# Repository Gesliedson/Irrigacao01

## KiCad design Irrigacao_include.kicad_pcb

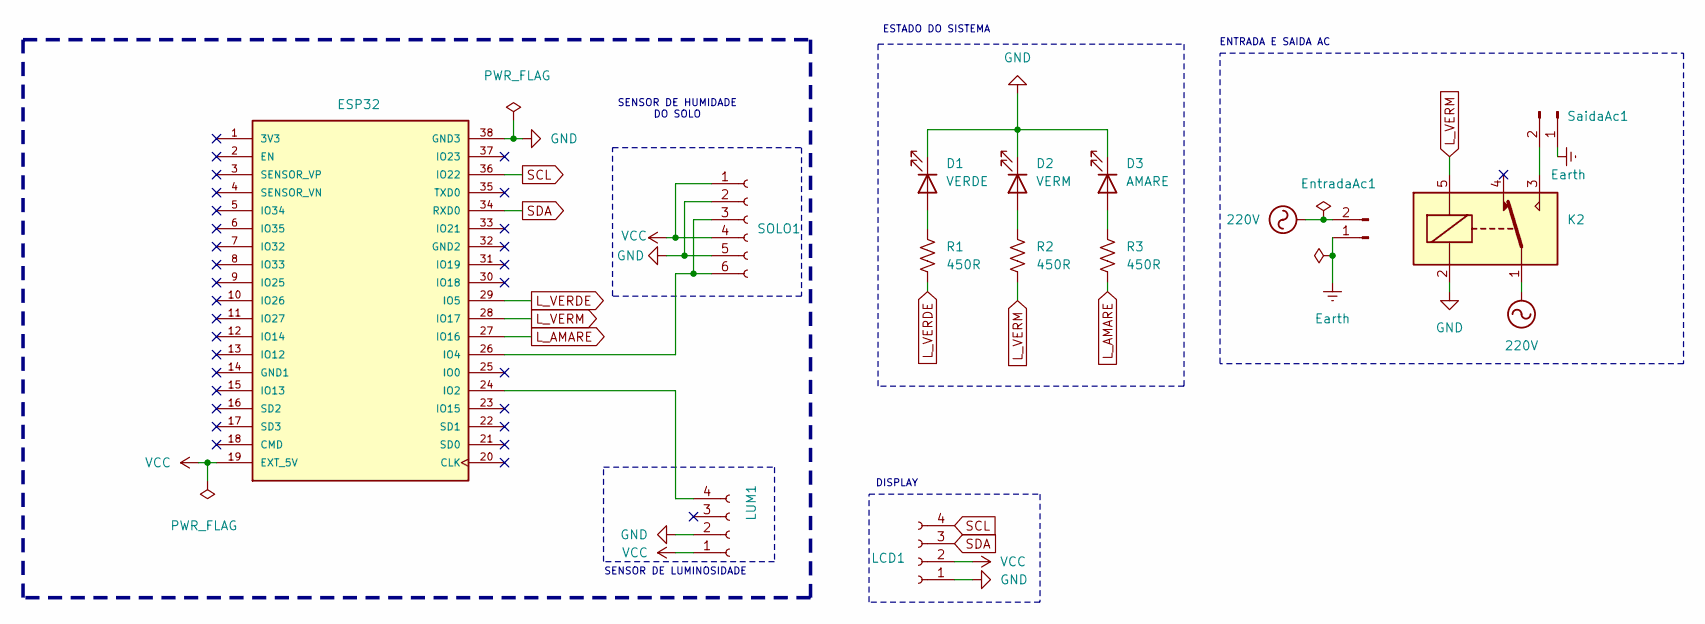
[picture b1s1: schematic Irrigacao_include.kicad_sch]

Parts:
D1: VERDE; LED_D3.0mm
D2: VERM; LED_D3.0mm
D3: AMARE; LED_D3.0mm
ESP32: DEVKIT_V1_ESP32-WROOM-32; MODULE_DEVKIT_V1_ESP32-WROOM-32; PARTREV N/A
EntradaAc1: Conn_01x02_Pin; PhoenixContact_GMSTBA_2,5_2-G_1x02_P7.50mm_Horizontal
K2: SANYOU_SRD_Form_C; Relay_SPDT_SANYOU_SRD_Series_Form_C
LCD1: Conn_01x04_Socket; PinSocket_1x04_P2.54mm_Horizontal
LUM1: Conn_01x04_Socket; PinSocket_1x04_P2.54mm_Horizontal
R1, R2, R3: 450R; R_Axial_DIN0207_L6.3mm_D2.5mm_P10.16mm_Horizontal
SOLO1: Conn_01x06_Socket; PinSocket_1x06_P2.54mm_Vertical
SaidaAc1: Conn_01x02_Pin; PhoenixContact_GMSTBA_2,5_2-G_1x02_P7.50mm_Horizontal

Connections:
220V: EntradaAc1.2, K2.1
Earth: EntradaAc1.1, SaidaAc1.1
GND: D1.1 (K), D2.1 (K), D3.1 (K), ESP32.38 (GND3), K2.2, LCD1.1, LUM1.2, SOLO1.2, SOLO1.5
L_AMARE: ESP32.27 (IO16), R3.2
L_VERDE: ESP32.29 (IO5), R1.2
L_VERM: ESP32.28 (IO17), K2.5, R2.2
unnamed: D1.2 (A), R1.1
unnamed: D2.2 (A), R2.1
unnamed: D3.2 (A), R3.1
unnamed: ESP32.24 (IO2), LUM1.4
unnamed: ESP32.26 (IO4), SOLO1.3, SOLO1.6
unnamed: K2.3, SaidaAc1.2
SCL: ESP32.36 (IO22), LCD1.4
SDA: ESP32.34 (RXD0), LCD1.3
VCC: ESP32.19 (EXT_5V), LCD1.2, LUM1.1, SOLO1.1, SOLO1.4

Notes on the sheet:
SENSOR DE HUMIDADE DO SOLO
DISPLAY
ESTADO DO SISTEMA
SENSOR DE LUMINOSIDADE
ENTRADA E SAIDA AC

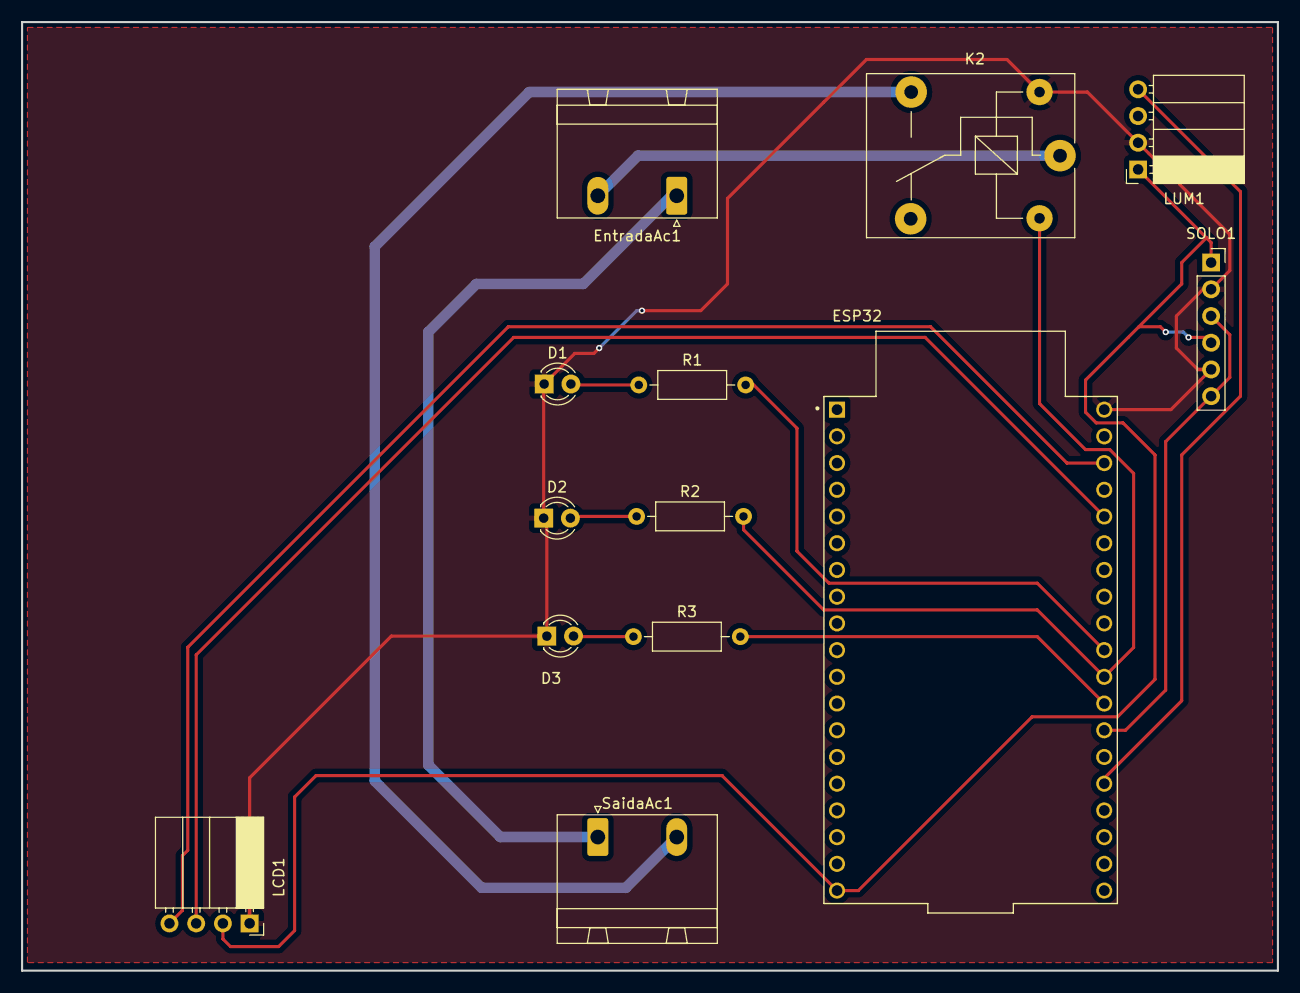
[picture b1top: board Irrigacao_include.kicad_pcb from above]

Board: 2 copper layers, 119.4 x 90.2 mm, 13 parts (0 on the bottom side), 15 nets.

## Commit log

2025-02-07 Projeto01
2025-02-07 Create PCB
2025-02-07 Add files via upload
    Arquivos úteis
2025-02-08 codigo do sitema
2025-02-08 CODIGO FINAL
